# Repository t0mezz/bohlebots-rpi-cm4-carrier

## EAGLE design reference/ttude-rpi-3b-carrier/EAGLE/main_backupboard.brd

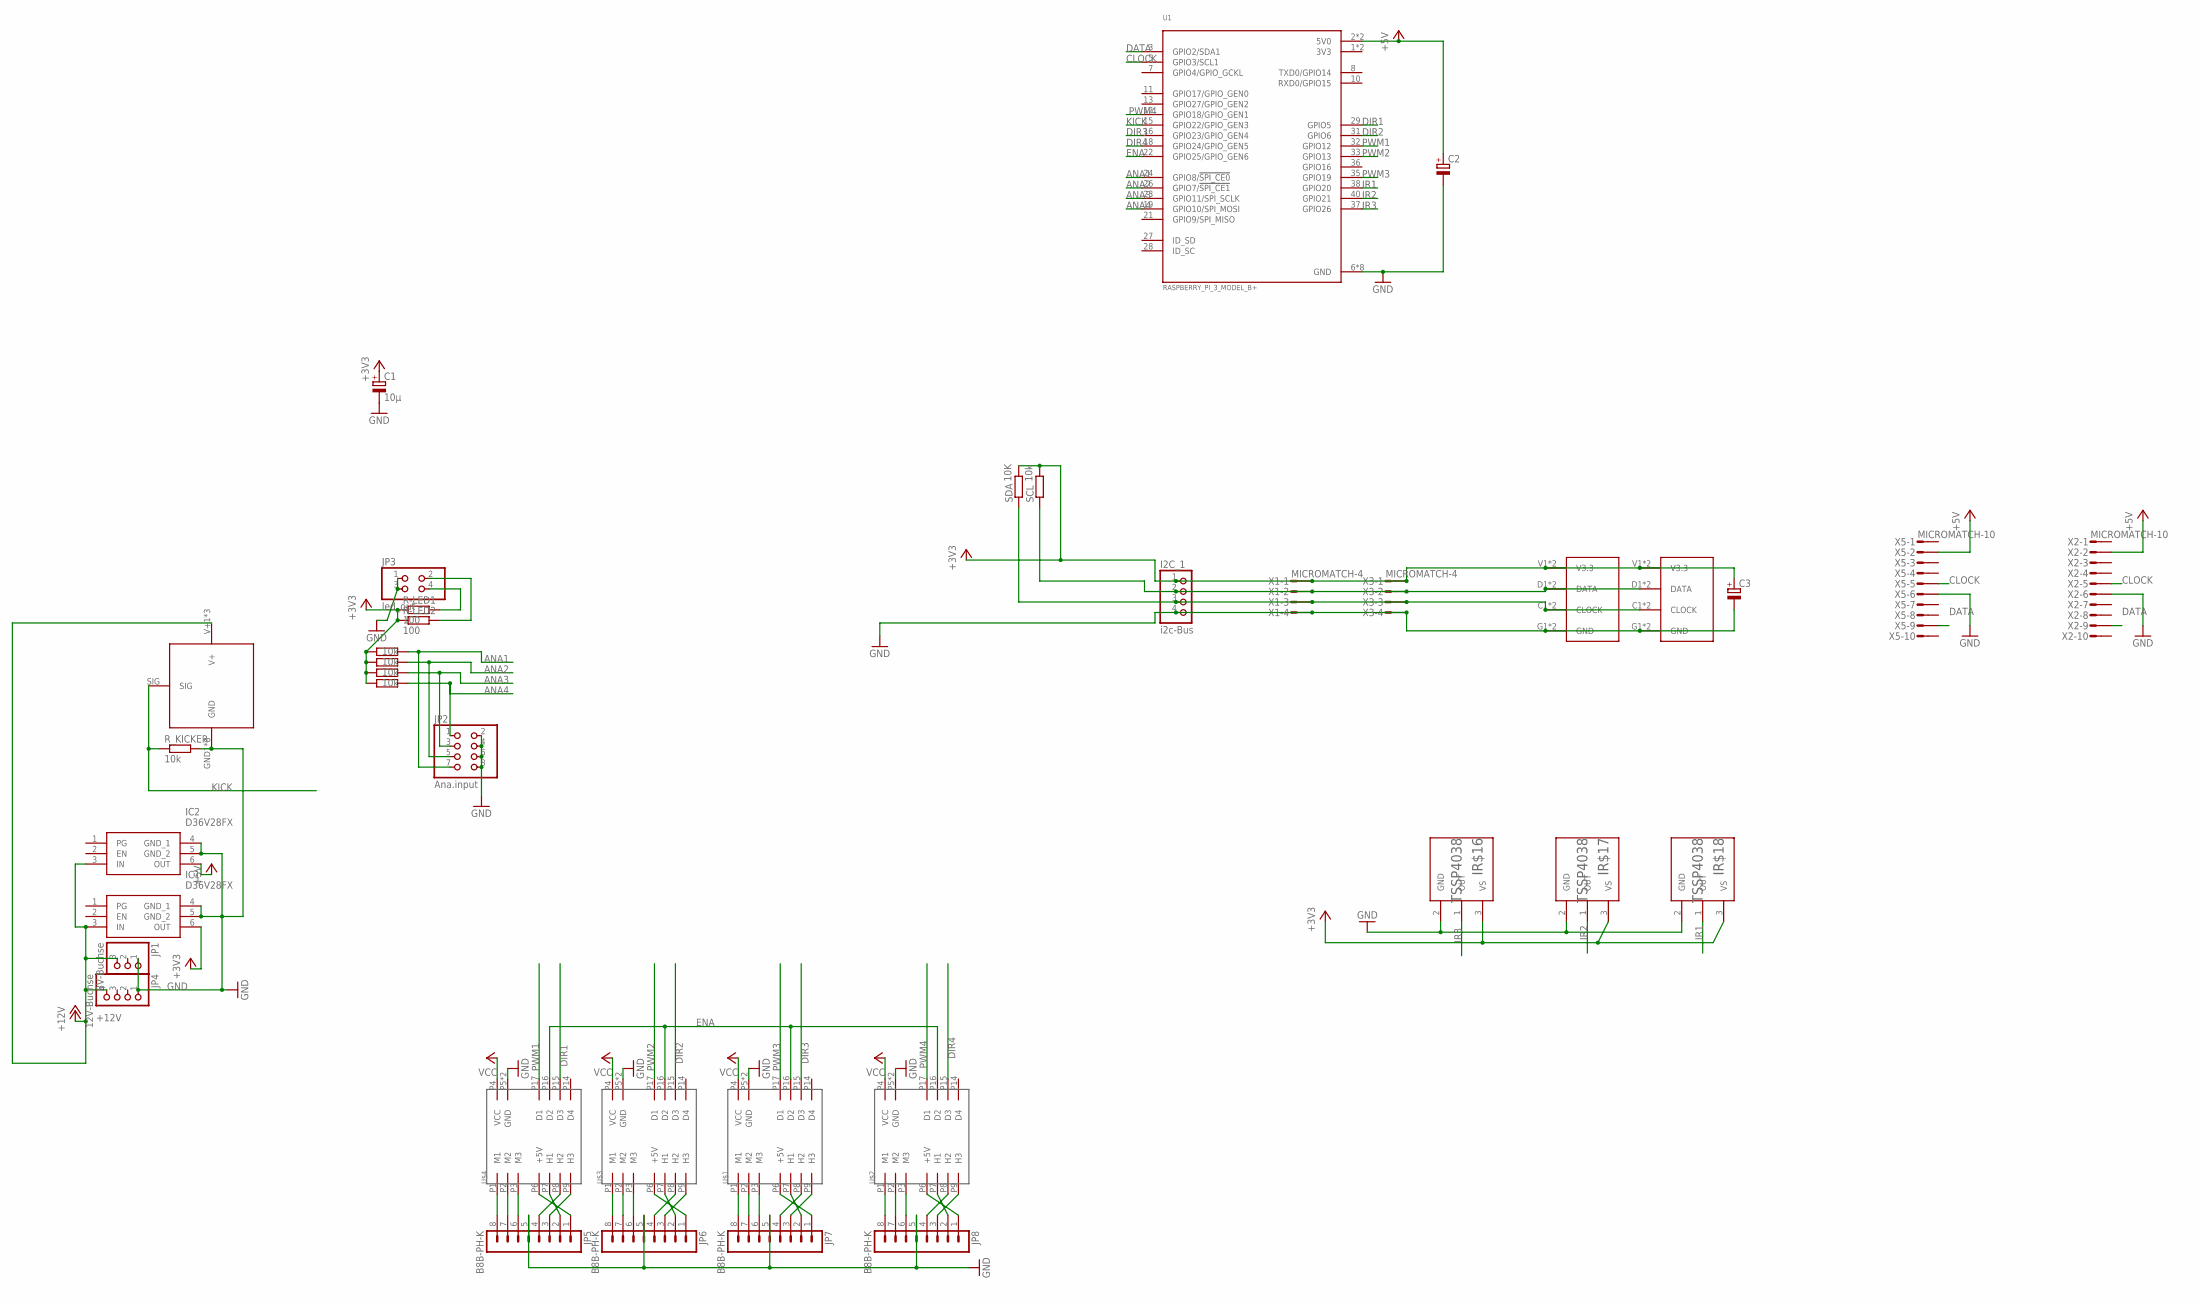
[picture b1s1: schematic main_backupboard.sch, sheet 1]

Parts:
C1: 10µ; E2,5-6E
C2, C3: CPOL-EUE2-5; E2-5
I2C_1: i2c-Bus; 1X04
IC1, IC2: D36V28FX
IR$16, IR$17, IR$18: TSSP4038; XDCR_TSSP4038
JP1: 8V-Buchse; 1X03
JP2: Ana.input; 2X04
JP3: led_out; 2X02
JP4: 12V-Buchse; 1X04
JP5, JP6, JP7, JP8: B8B-PH-K
R-LED1, R-LED2: 100; 0207/10
R_AD14, R_AD25, R_AD26, R_AD27: 10k; 0207/10
R_KICKER: 10k; 0207/10
SCL: 10k; 0207/10
SDA: 10K; 0207/10
U1: RASPBERRY_PI_3_MODEL_B+; MODULE_RASPBERRY_PI_3_MODEL_B+
U$1, U$2, U$3, U$4: 24/2
U$8, U$9: TASTER_LED
U$17: KICKER
X1, X3: MICROMATCH-4
X2, X5: MICROMATCH-10

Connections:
3V3: U1.1 (3V3), U1.17 (3V3)
+3V3: C1.+, C3.+, I2C_1.1, IC1.6 (OUT), IR$16.3 (VS), IR$17.3 (VS), IR$18.3 (VS), R-LED1.1, R-LED2.1, R_AD14.1, R_AD25.1, R_AD26.1, R_AD27.1, SCL.2, SDA.2, U$8.V1 (V3.3), U$8.V2 (V3.3), U$9.V1 (V3.3), U$9.V2 (V3.3), X1.1, X3.1
+5V: C2.+, IC2.6 (OUT), U1.2 (5V0), U1.4 (5V0), X2.2, X5.2
+12V: IC1.3 (IN), IC2.3 (IN), JP1.3, JP4.4, U$1.P4 (VCC), U$2.P4 (VCC), U$3.P4 (VCC), U$4.P4 (VCC), U$17.V+1 (V+), U$17.V+2 (V+), U$17.V+3 (V+)
ANA1: JP2.7, R_AD25.2, U1.24 (GPIO8/!SPI_CE0!)
ANA2: JP2.5, R_AD26.2, U1.26 (GPIO7/!SPI_CE1!)
ANA3: JP2.3, R_AD27.2, U1.23 (GPIO11/SPI_SCLK)
ANA4: JP2.1, R_AD14.2, U1.19 (GPIO10/SPI_MOSI)
CLOCK: I2C_1.3, SDA.1, U1.5 (GPIO3/SCL1), U$8.C1 (CLOCK), U$8.C2 (CLOCK), U$9.C1 (CLOCK), U$9.C2 (CLOCK), X1.3, X2.5, X3.3, X5.5
DATA: I2C_1.2, SCL.1, U1.3 (GPIO2/SDA1), U$8.D1 (DATA), U$8.D2 (DATA), U$9.D1 (DATA), U$9.D2 (DATA), X1.2, X2.9, X3.2, X5.9
DIR1: U1.29 (GPIO5), U$4.P15 (D3)
DIR2: U1.31 (GPIO6), U$3.P15 (D3)
DIR3: U1.16 (GPIO23/GPIO_GEN4), U$1.P15 (D3)
DIR4: U1.18 (GPIO24/GPIO_GEN5), U$2.P15 (D3)
ENA: U1.22 (GPIO25/GPIO_GEN6), U$1.P16 (D2), U$2.P16 (D2), U$3.P16 (D2), U$4.P16 (D2)
GND: C1.-, C2.-, C3.-, I2C_1.4, IC1.4 (GND_1), IC1.5 (GND_2), IC2.4 (GND_1), IC2.5 (GND_2), IR$16.2 (GND), IR$17.2 (GND), IR$18.2 (GND), JP1.1, JP2.2, JP2.4, JP2.6, JP2.8, JP3.1, JP3.3, JP4.1, JP5.5, JP6.5, JP7.5, JP8.5, R_KICKER.2, U1.6 (GND), U1.9 (GND), U1.14 (GND), U1.20 (GND), U1.25 (GND), U1.30 (GND), U1.34 (GND), U1.39 (GND), U$1.P5 (GND), U$1.P18 (GND), U$2.P5 (GND), U$2.P18 (GND), U$3.P5 (GND), U$3.P18 (GND), U$4.P5 (GND), U$4.P18 (GND), U$8.G1 (GND), U$8.G2 (GND), U$9.G1 (GND), U$9.G2 (GND), U$17.GND1 (GND), U$17.GND2 (GND), U$17.GND3 (GND), U$17.GND4 (GND), U$17.GND5 (GND), U$17.GND6 (GND), U$17.GND7 (GND), U$17.GND8 (GND), X1.4, X2.6, X3.4, X5.6
IR1: IR$18.1 (OUT), U1.38 (GPIO20)
IR2: IR$17.1 (OUT), U1.40 (GPIO21)
IR3: IR$16.1 (OUT), U1.37 (GPIO26)
KICK: R_KICKER.1, U1.15 (GPIO22/GPIO_GEN3), U$17.SIG
unnamed: JP5.8, U$4.P1 (M1)
unnamed: JP5.7, U$4.P2 (M2)
unnamed: JP3.4, R-LED1.2
unnamed: JP3.2, R-LED2.2
unnamed: JP5.6, U$4.P3 (M3)
unnamed: JP6.8, U$3.P1 (M1)
unnamed: JP6.7, U$3.P2 (M2)
unnamed: JP6.6, U$3.P3 (M3)
unnamed: JP7.8, U$1.P1 (M1)
unnamed: JP7.7, U$1.P2 (M2)
unnamed: JP7.6, U$1.P3 (M3)
unnamed: JP8.8, U$2.P1 (M1)
unnamed: JP8.7, U$2.P2 (M2)
unnamed: JP8.6, U$2.P3 (M3)
unnamed: JP5.1, U$4.P6 (+5V)
unnamed: JP6.1, U$3.P6 (+5V)
unnamed: JP7.1, U$1.P6 (+5V)
unnamed: JP8.1, U$2.P6 (+5V)
unnamed: JP5.2, U$4.P7 (H1)
unnamed: JP5.3, U$4.P9 (H3)
unnamed: JP5.4, U$4.P8 (H2)
unnamed: JP6.2, U$3.P7 (H1)
unnamed: JP6.3, U$3.P9 (H3)
unnamed: JP6.4, U$3.P8 (H2)
unnamed: JP7.2, U$1.P7 (H1)
unnamed: JP7.3, U$1.P9 (H3)
unnamed: JP7.4, U$1.P8 (H2)
unnamed: JP8.2, U$2.P7 (H1)
unnamed: JP8.3, U$2.P9 (H3)
unnamed: JP8.4, U$2.P8 (H2)
PWM1: U1.32 (GPIO12), U$4.P17 (D1)
PWM2: U1.33 (GPIO13), U$3.P17 (D1)
PWM3: U1.35 (GPIO19), U$1.P17 (D1)
PWM4: U1.12 (GPIO18/GPIO_GEN1), U$2.P17 (D1)

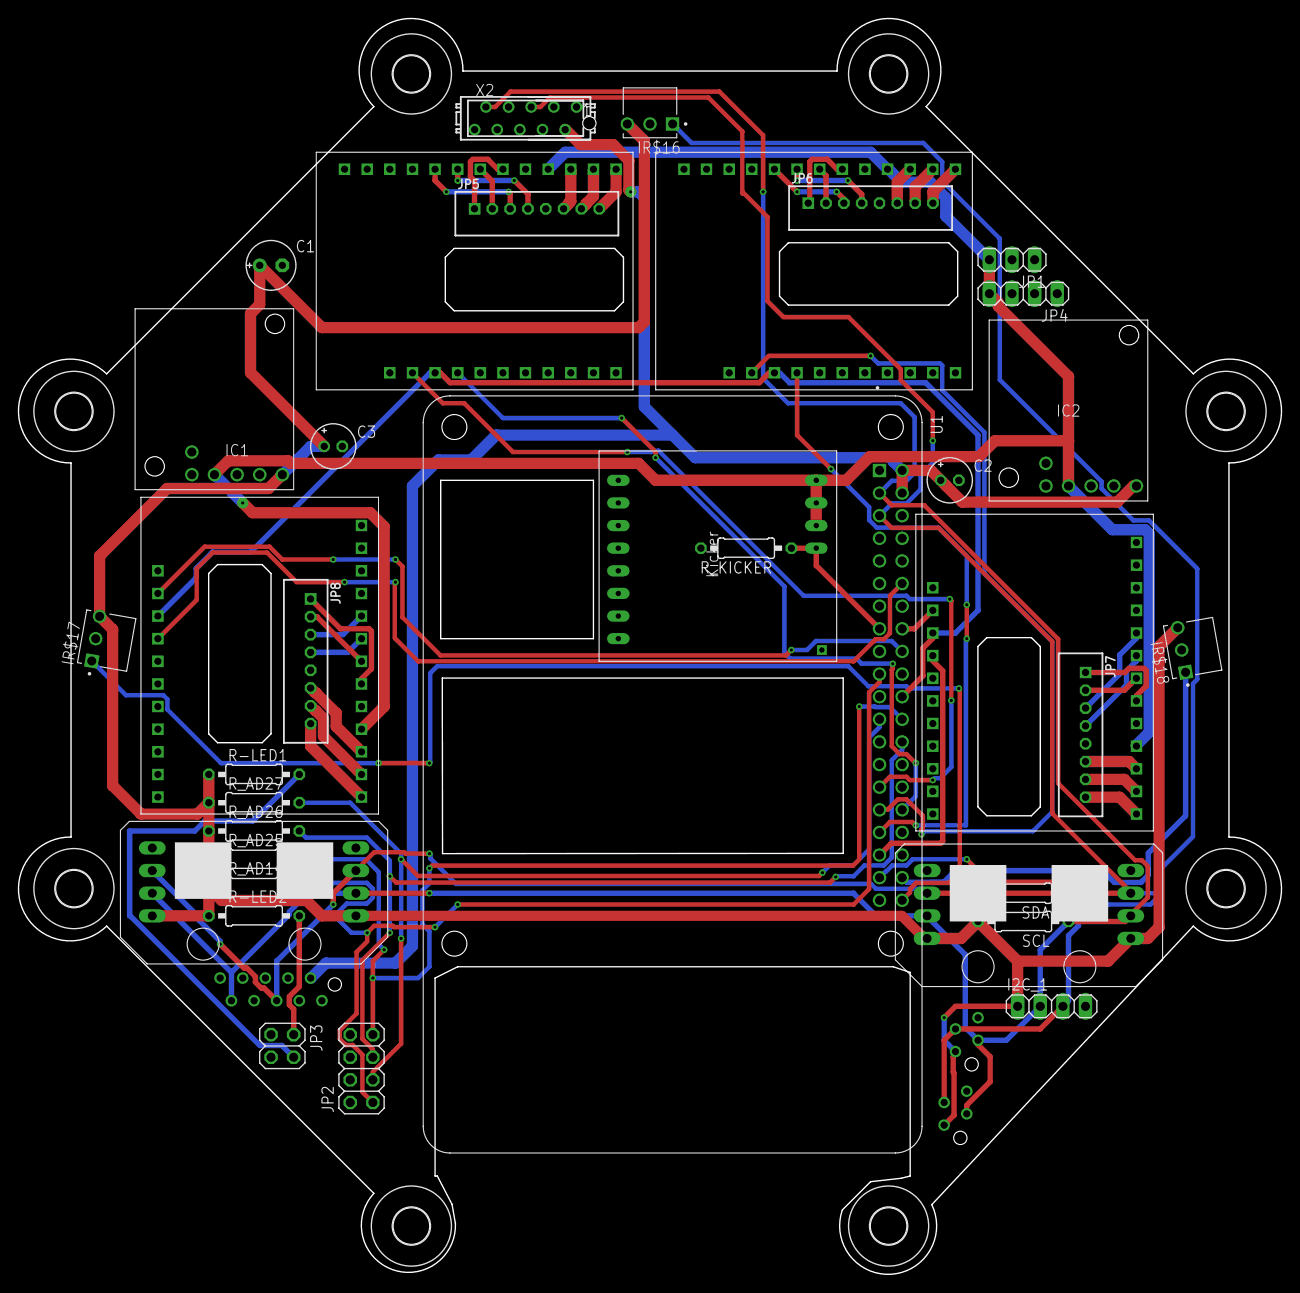
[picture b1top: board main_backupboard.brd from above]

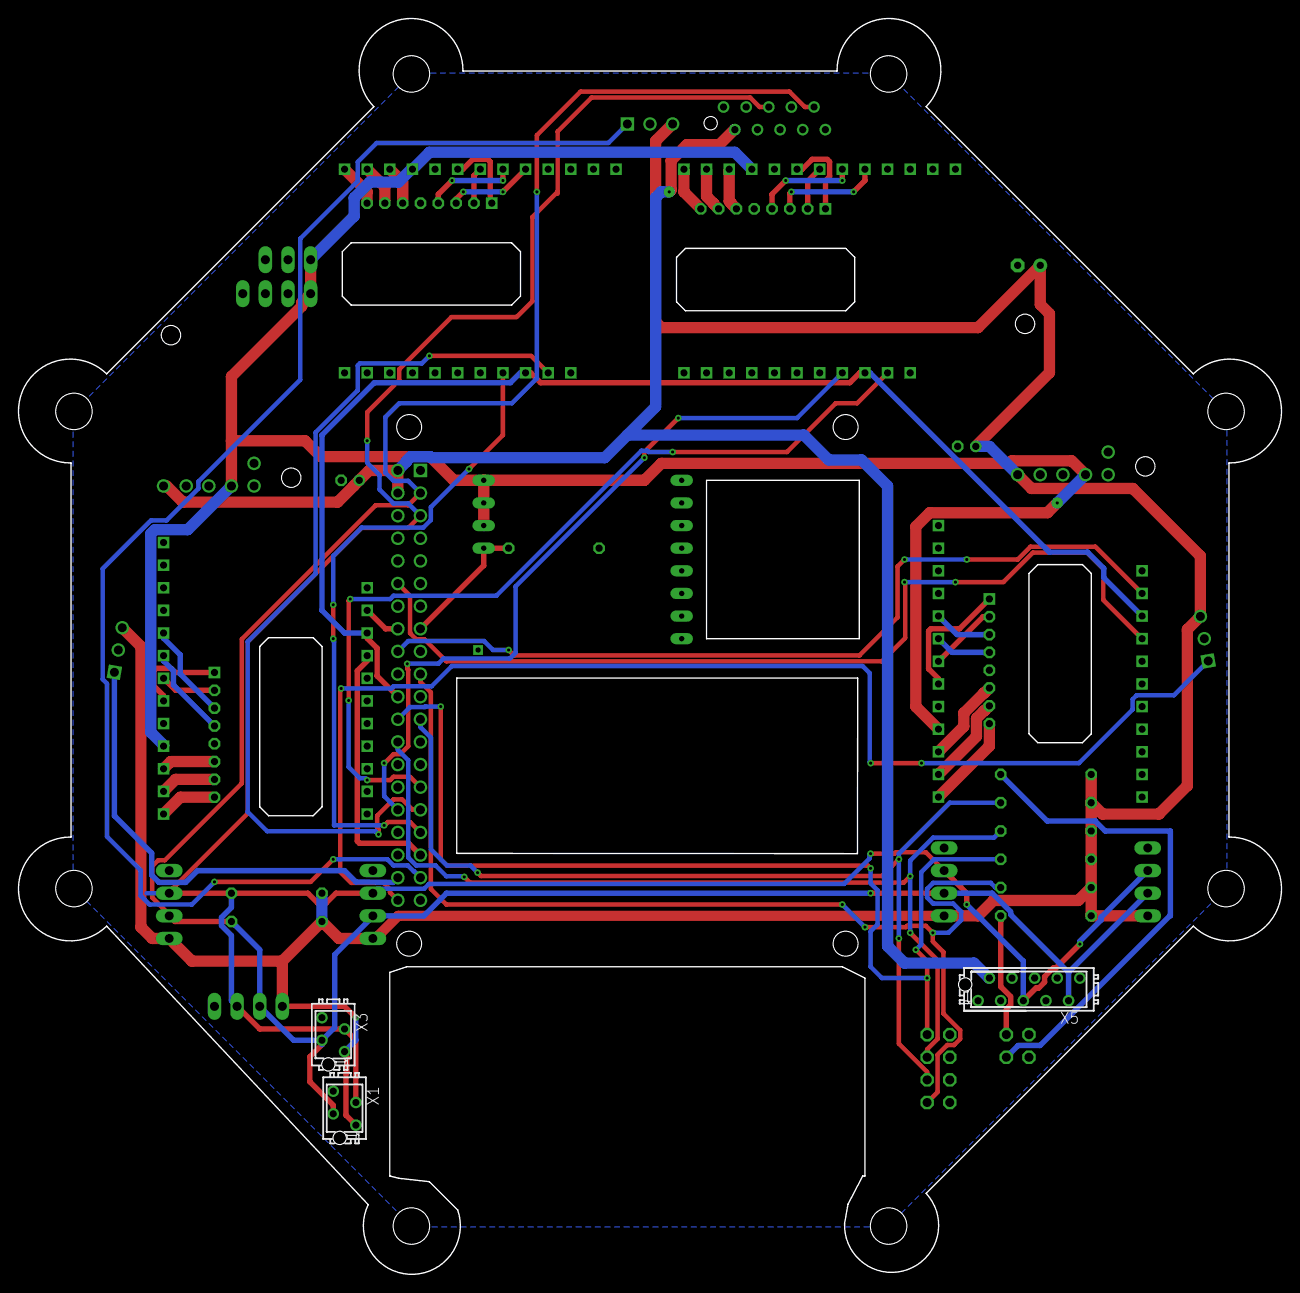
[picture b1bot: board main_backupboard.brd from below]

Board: 2 copper layers, 141.8 x 141.0 mm, 46 parts (3 on the bottom side), 54 nets.

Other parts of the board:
U$5, U$6, U$7, U$10, U$11, U$12, U$13, U$14: 4,1

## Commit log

2023-12-05 Schaltplan Update
2023-12-05 Test change
2023-12-05 Schematic Update
2023-12-06 Random changes.
2023-12-06 Added USB and i2c connector for groundsensor.
2023-12-06 Added Motordrivers.
2023-12-06 Save.
2023-12-07 Added step downs.
2023-12-07 Added I2C pullup
2023-12-08 Some small changes, probably first finished schematic.
2023-12-10 Finished Schematic, started pcb.
2023-12-10 Some configuartions for pcb.
2023-12-11 Added esd protection TODO: find fitting tvs diode (tht) 2p, 4p
2023-12-13 Added tsv diodes.
2023-12-13 Started routing.
2023-12-13 PCB Layout Update.
2023-12-21 Updated pcb layout.
2023-12-27 IC placement done.
2023-12-29 V01 finished.
2024-01-01 V01.2 Update.
2024-01-18 Added dxf files.
2024-01-18 Renames.
2024-01-18 Renames again.
2024-01-19 Added some vias.
2024-01-19 Added some file system changes.
2024-01-19 test
2024-01-19 test2
2024-01-19 Added qr-c, fixed 'single connector footpring' issue, added compensation vias.
2024-01-19 Updated render img.
2024-01-21 v2.0 finished.

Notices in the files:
parts and their libraries:
con-jst-ph: Copyright (C) 2016, Bob Starr
